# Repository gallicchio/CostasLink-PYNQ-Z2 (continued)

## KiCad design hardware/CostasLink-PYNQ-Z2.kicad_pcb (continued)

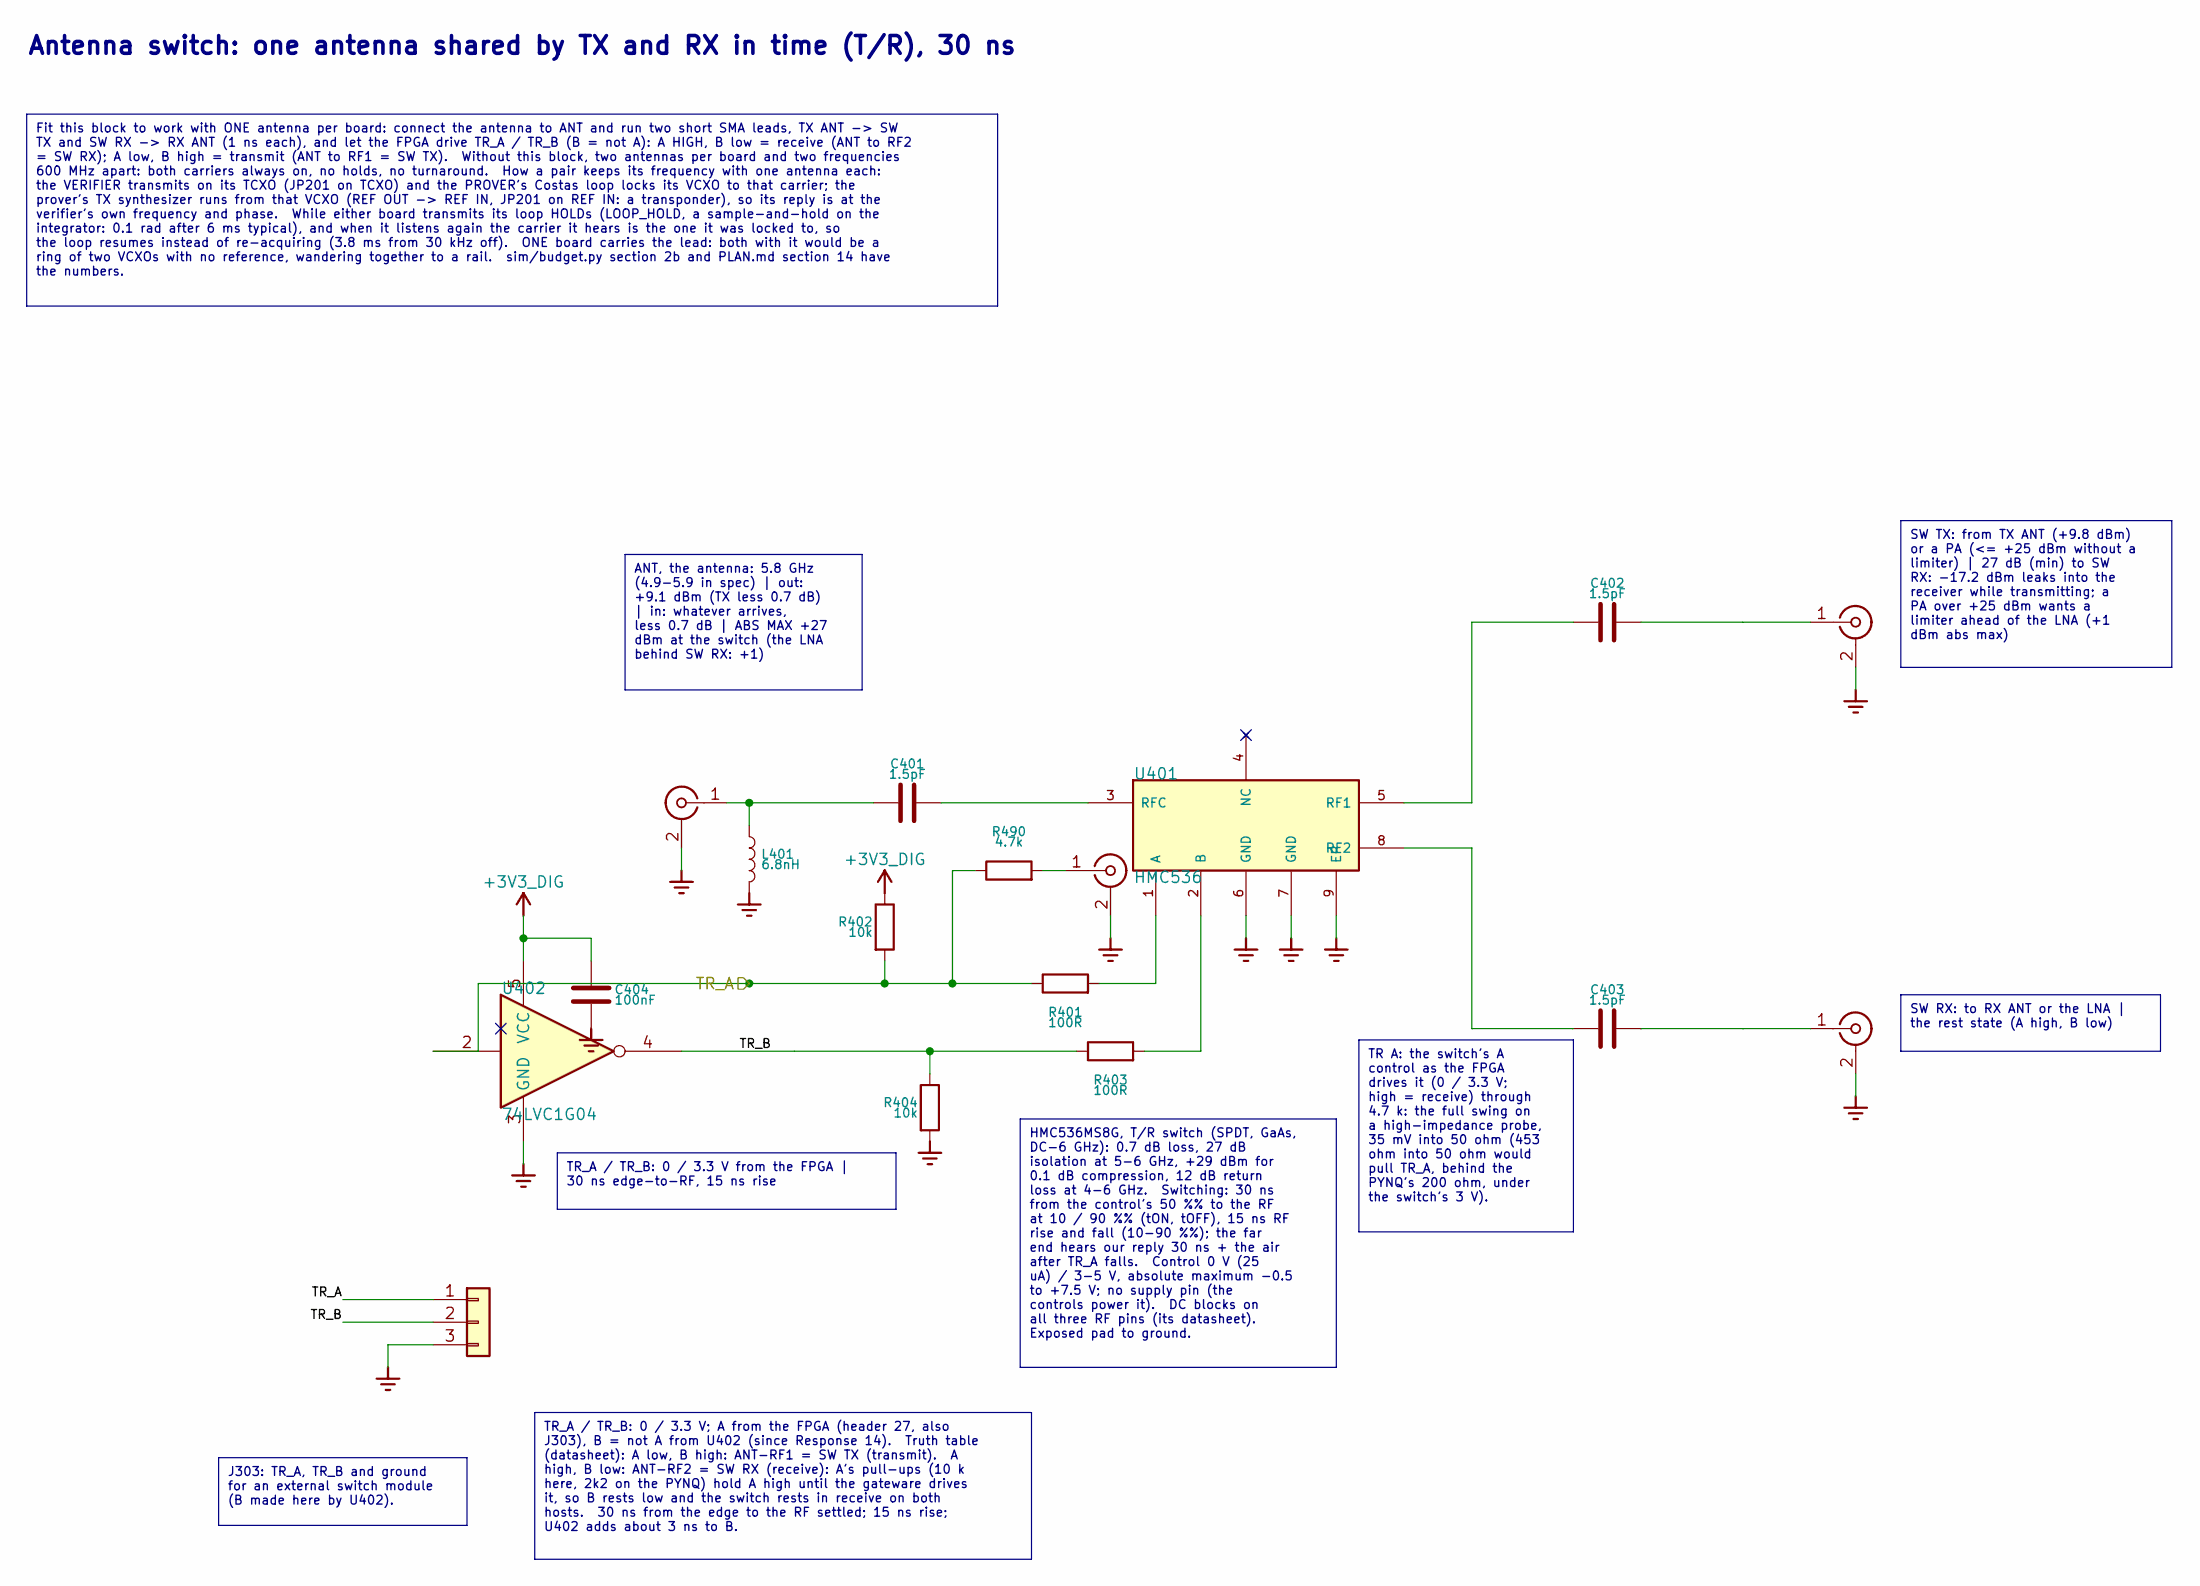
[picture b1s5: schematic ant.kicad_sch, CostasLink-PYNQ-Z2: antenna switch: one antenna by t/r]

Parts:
C401, C402, C403: 1.5pF; C_0402_1005Metric; MPN 0402CG1R5C500NT; LCSC C1552
C404: 100nF; C_0402_1005Metric; MPN CL05B104KO5NNNC; LCSC C1525
J303: TR; PinHeader_1x03_P2.54mm_Vertical; MPN PZ254V-11-03P; LCSC C2937625
J401: ANT; SMA_BWSMA-KWE-Z001; MPN BWSMA-KWE-Z001; LCSC C496551
J402: SW TX; SMA_BWSMA-KWE-Z001; MPN BWSMA-KWE-Z001; LCSC C496551
J403: SW RX; SMA_BWSMA-KWE-Z001; MPN BWSMA-KWE-Z001; LCSC C496551
J490: TR A; MMCX_BWMMCX-KE_Vertical; MPN BWMMCX-KE; LCSC C5137198
L401: 6.8nH; L_0402_1005Metric; MPN LQW15AN6N8G00D; LCSC C82919
R401, R403: 100R; R_0402_1005Metric; MPN 0402WGF1000TCE; LCSC C25076
R402, R404: 10k; R_0402_1005Metric; MPN 0402WGF1002TCE; LCSC C25744
R490: 4.7k; R_0402_1005Metric; MPN 0402WGF4701TCE; LCSC C25900
U401: HMC536; MSOP-8-1EP_3x3mm_P0.65mm_EP1.73x1.85mm; MPN HMC536MS8G; LCSC C17271830
U402: 74LVC1G04; SOT-353_SC-70-5; MPN SN74LVC1G04DCKR; LCSC C8207

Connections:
+3V3_DIG: C404.1, R402.1, U402.5 (VCC); also elsewhere on the board
/Antenna switch: one antenna by T/R/TR_A: J303.1, R401.1, R402.2, R490.1, U402.2; also elsewhere on the board
/Antenna switch: one antenna by T/R/TR_B: J303.2, R403.1, R404.1, U402.4
unnamed: C401.1, J401.1 (In), L401.1
unnamed: C402.2, J402.1 (In)
unnamed: C403.2, J403.1 (In)
unnamed: J490.1 (In), R490.2
unnamed: R401.2, U401.1 (A)
unnamed: R403.2, U401.2 (B)
unnamed: C402.1, U401.5 (RF1)
unnamed: C403.1, U401.8 (RF2)
unnamed: C401.2, U401.3 (RFC)

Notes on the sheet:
Antenna switch: one antenna shared by TX and RX in time (T/R), 30 ns
Fit this block to work with ONE antenna per board: connect the antenna to ANT and run two short SMA leads, TX ANT -> SW TX and SW RX -> RX ANT (1 ns each), and let the FPGA drive TR_A / TR_B (B = not A): A HIGH, B low = receive (ANT to RF2 = SW RX); A low, B high = transmit (ANT to RF1 = SW TX). Wi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
ANT, the antenna: 5.8 GHz (4.9-5.9 in spec) | out: +9.1 dBm (TX less 0.7 dB) | in: whatever arrives, less 0.7 dB | ABS MAX +27 dBm at the switch (the LNA behind SW RX: +1)
SW TX: from TX ANT (+9.8 dBm) or a PA (<= +25 dBm without a limiter) | 27 dB (min) to SW RX: -17.2 dBm leaks into the receiver while transmitting; a PA over +25 dBm wants a limiter ahead of the LNA (+1 dBm abs max)
SW RX: to RX ANT or the LNA | the rest state (A high, B low)
J303: TR_A, TR_B and ground for an external switch module (B made here by U402).
TR_A / TR_B: 0 / 3.3 V from the FPGA | 30 ns edge-to-RF, 15 ns rise
TR_A / TR_B: 0 / 3.3 V; A from the FPGA (header 27, also J303), B = not A from U402 (since Response 14). Truth table (datasheet): A low, B high: ANT-RF1 = SW TX (transmit). A high, B low: ANT-RF2 = SW RX (receive): A's pull-ups (10 k here, 2k2 on the PYNQ) hold A high until the gateware drives it, 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
HMC536MS8G, T/R switch (SPDT, GaAs, DC-6 GHz): 0.7 dB loss, 27 dB isolation at 5-6 GHz, +29 dBm for 0.1 dB compression, 12 dB return loss at 4-6 GHz. Switching: 30 ns from the control's 50 %% to the RF at 10 / 90 %% (tON, tOFF), 15 ns RF rise and fall (10-90 %%); the far end hears our reply 30 ns +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
TR A: the switch's A control as the FPGA drives it (0 / 3.3 V; high = receive) through 4.7 k: the full swing on a high-impedance probe, 35 mV into 50 ohm (453 ohm into 50 ohm would pull TR_A, behind the PYNQ's 200 ohm, under the switch's 3 V).
